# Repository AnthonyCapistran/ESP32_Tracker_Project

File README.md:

# ESP32 UDP Face Tracker

Real-time face detection and pan/tilt tracking script in Python using OpenCV and UDP commands sent to an ESP32 controller.

This is the software side of my Smart Face-Tracking Fan, an undergraduate research project at UT Dallas (UR@ECE, Spring 2026).

## System Overview

The project uses two ESP32 boards and a computer running Python:

| Component | Role |
|---|---|
| ESP32-S3 with camera attachment | Captures video and provides the camera stream |
| Python script (`esp32_face_tracker.py`) | Reads the stream, detects and tracks faces with OpenCV, and sends pan/tilt commands over UDP |
| ESP32-WROOM | Receives the commands and drives the pan/tilt motors |

The ESP32-S3 and ESP32-WROOM boards communicate with each other over ESP-NOW.

```
ESP32-S3 camera --(video stream)--> Python + OpenCV --(UDP "x,y")--> ESP32-WROOM --> pan/tilt motors
        \_________________________ ESP-NOW _________________________/
```

## How It Works

- Reads video frames from `STREAM_URL` and flips the image to match camera orientation.
- Detects faces using OpenCV's Caffe DNN detector (`deploy.prototxt` and `res10_300x300_ssd_iter_140000.caffemodel`), falling back to a Haar cascade if the DNN files are unavailable.
- Smooths horizontal and vertical face-center offsets using a rolling window, applies deadzone and gain/step limits, and sends `"x,y"` movement commands over UDP to `WROOM_IP:UDP_PORT`.
- Supports locking onto a specific face by size and position, entering an idle search sweep after `IDLE_TIMEOUT`, and re-acquiring a matching target size.

## Setup & Usage

1. Install dependencies:
   ```bash
   pip install opencv-python numpy
   ```
2. Place the DNN model files (`deploy.prototxt` and `res10_300x300_ssd_iter_140000.caffemodel`) next to the script. Without them, the script falls back to the Haar cascade.
3. Edit the configuration values at the top of `esp32_face_tracker.py`:
   - `STREAM_URL`: URL of the ESP32-S3 camera stream
   - `WROOM_IP`: IP address of the ESP32-WROOM
   - `UDP_PORT`: UDP port the ESP32-WROOM listens on
   - `IDLE_TIMEOUT`: seconds without a face before the idle search sweep starts
4. Flash the ESP32 firmware from the firmware folders in this repo.
5. Run the tracker:
   ```bash
   python esp32_face_tracker.py
   ```

## Repository Contents

- `esp32_face_tracker.py`: Python face detection and UDP command sender
- `SMART_FAN_PROJECT_CODE/`: ESP32 camera, pan/tilt, and motor Arduino sketches and libraries
- `Smart Fan/`: Hardware, PCB, and mechanical mount files for the Smart Fan build
- `CREDITS.md`: Attribution for third-party files

## Tools

Python, OpenCV, NumPy, C/C++ (ESP32 firmware), FreeRTOS, ESP-NOW, UDP

## Credits

The pan/tilt mount files are by isaac879. See `CREDITS.md` for attribution.

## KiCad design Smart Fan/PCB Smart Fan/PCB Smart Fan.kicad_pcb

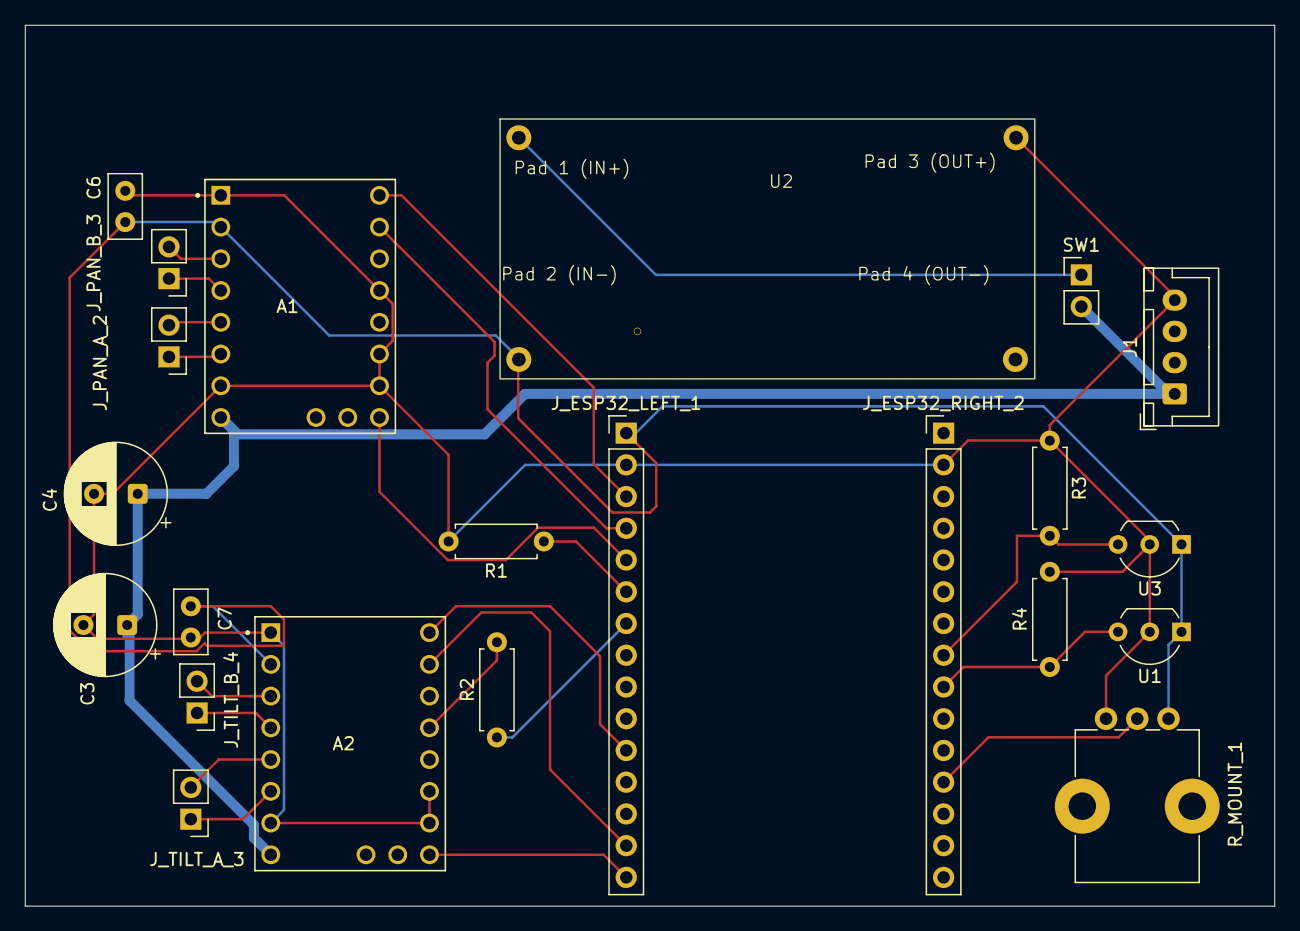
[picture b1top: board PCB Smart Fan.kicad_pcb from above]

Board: 2 copper layers, 100.0 x 70.5 mm, 22 parts (0 on the bottom side), 24 nets.

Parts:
A1: TMC2209_pan_1; TMC2209_pan
A2: TMC2209_TILT_1; TMC2209 TILT
C3, C4: 100uF; CP_Radial_D8.0mm_P3.50mm
C6, C7: 100nF; C_Disc_D5.0mm_W2.5mm_P2.50mm
J1: Conn_01x04_Pin; JST_XH_B4B-XH-A_1x04_P2.50mm_Vertical
J_ESP32_LEFT_1: Conn_01x15; PinHeader_1x15_P2.54mm_Vertical
J_ESP32_RIGHT_2: Conn_01x15; PinHeader_1x15_P2.54mm_RIGHT
J_PAN_A_2: Conn_01x02; PinHeader_1x02_P2.54mm_Vertical
J_PAN_B_3: Conn_01x02; PinHeader_1x02_P2.54mm_Vertical
J_TILT_A_3: Conn_01x02; PinHeader_1x02_P2.54mm_Vertical
J_TILT_B_4: Conn_01x02; PinHeader_1x02_P2.54mm_Vertical
R1, R2: 1k; R_Axial_DIN0207_L6.3mm_D2.5mm_P7.62mm_Horizontal
R3: 10k; R_Axial_DIN0207_L6.3mm_D2.5mm_P7.62mm_Horizontal
R4: 10K; R_Axial_DIN0207_L6.3mm_D2.5mm_P7.62mm_Horizontal
R_MOUNT_1: 10k_Potentiometer; Potentiometer_Bourns_PTV09A-1_Single_Vertical
SW1: SW_Push; PinHeader_1x02_P2.54mm_Vertical
U1, U3: A3144H; TO-92_Inline_Wide
U2: LM2596S-3.3; LM2596_Module.kicad_mod

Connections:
+3.3V: A1.2 (VDD), A2.2 (VDD), C6.1, C7.1, J_ESP32_LEFT_1.1, R_MOUNT_1.3, U1.1 (V_{CC}), U2.2 (OUT), U3.1 (V_{CC})
+12V: A1.8 (VMOT), A2.8 (VMOT), C3.1, C4.1, J1.1, SW1.2
/DIR_PAN: A1.16 (DIR), J_ESP32_LEFT_1.3
/DIR_TILT: A2.16 (DIR), J_ESP32_LEFT_1.11
/HALL_PAN: J_ESP32_RIGHT_2.23 (D25), R3.2, U3.3 (V_{OUT})
/HALL_TILT: J_ESP32_RIGHT_2.24 (D33), R4.1, U1.3 (V_{OUT})
/PAN_COIL_A+: A1.3 (1B), J_PAN_A_2.1
/PAN_COIL_A-: A1.4 (1A), J_PAN_A_2.2
/PAN_COIL_B+: A1.5 (2A), J_PAN_B_3.1
/PAN_COIL_B-: A1.6 (2B), J_PAN_B_3.2
/POT_MOUNT: J_ESP32_RIGHT_2.27 (D34), R_MOUNT_1.2
/STEP_PAN: A1.15 (STEP), J_ESP32_LEFT_1.4
/STEP_TILT: A2.15 (STEP), J_ESP32_LEFT_1.14
/TILT_COIL_A+: A2.3 (1B), J_TILT_A_3.1
/TILT_COIL_A-: A2.4 (1A), J_TILT_A_3.2
/TILT_COIL_B+: A2.5 (2A), J_TILT_B_4.1
/TILT_COIL_B-: A2.6 (2B), J_TILT_B_4.2
GND: A1.1 (GND), A1.7 (GND), A1.10 (MS1), A1.11 (MS2), A1.12 (MS3), A2.1 (GND), A2.7 (GND), A2.10 (MS1), A2.11 (MS2), C3.2, C4.2, C6.2, C7.2, J1.4, J_ESP32_LEFT_1.2, J_ESP32_RIGHT_2.17 (GND), R1.2, R3.1, R4.2, R_MOUNT_1.1, U1.2 (GND), U2.3 (GND), U3.2 (GND)
unnamed: A1.9 (~ENABLE), J_ESP32_LEFT_1.5
unnamed: A2.12 (MS3), R2.2
unnamed: A2.9 (~ENABLE), J_ESP32_LEFT_1.15
unnamed: J_ESP32_LEFT_1.6, R1.1
unnamed: J_ESP32_LEFT_1.7, R2.1
unnamed: SW1.1, U2.1 (VIN)

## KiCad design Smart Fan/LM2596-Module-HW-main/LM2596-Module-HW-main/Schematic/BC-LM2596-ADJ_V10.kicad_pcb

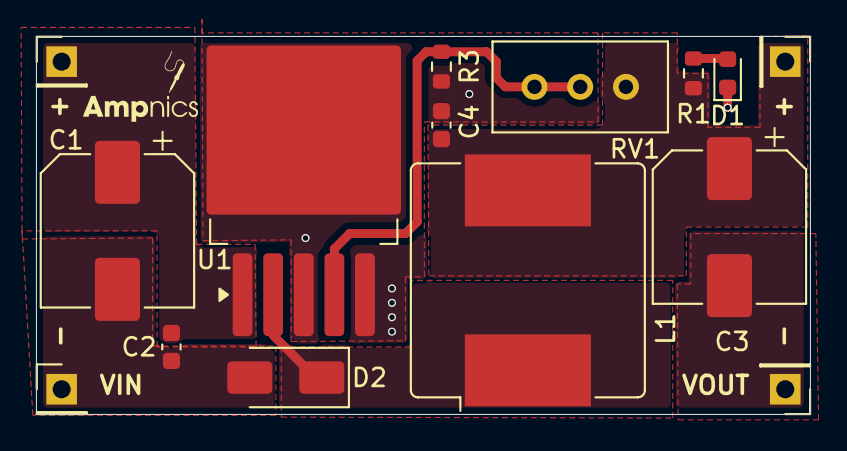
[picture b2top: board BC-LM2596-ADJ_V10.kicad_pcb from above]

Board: 2 copper layers, 43.0 x 21.0 mm, 15 parts (0 on the bottom side), 6 nets.

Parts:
C1: 100uF; CP_Elec_8x10
C2, C4: 100nF; C_0603_1608Metric
C3: 220uF; CP_Elec_8x10
D1: LED; LED_0603_1608Metric
D2: SS34; D_SMA
J1, J2, J3, J4: Conn_01x01_Pin; PinHeader_1x01_P2.54mm_Vertical
L1: 47uH; L_Bourns_SRR1208_12.7x12.7mm
R1: 4K7; R_0603_1608Metric
R3: 1K; R_0603_1608Metric
RV1: 10K; Potentiometer_Bourns_3296W_Vertical
U1: LM2596S-ADJ; TO-263-5_TabPin3

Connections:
/SW: D2.1 (K), L1.1, U1.2 (OUT)
/VIN: C1.1, C2.1, J1.1, U1.1 (VIN)
/VOUT: C3.1, C4.1, J3.1, L1.2, R1.1, RV1.1
GND: C1.2, C2.2, C3.2, C4.2, D1.1 (K), D2.2 (A), J2.1, J4.1, R3.2, U1.3 (GND), U1.5 (~ON/OFF)
unnamed: D1.2 (A), R1.2
unnamed: R3.1, RV1.2, RV1.3, U1.4 (FB)
